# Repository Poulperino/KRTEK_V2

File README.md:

# KRTEK_V2

On essaie on verra bien

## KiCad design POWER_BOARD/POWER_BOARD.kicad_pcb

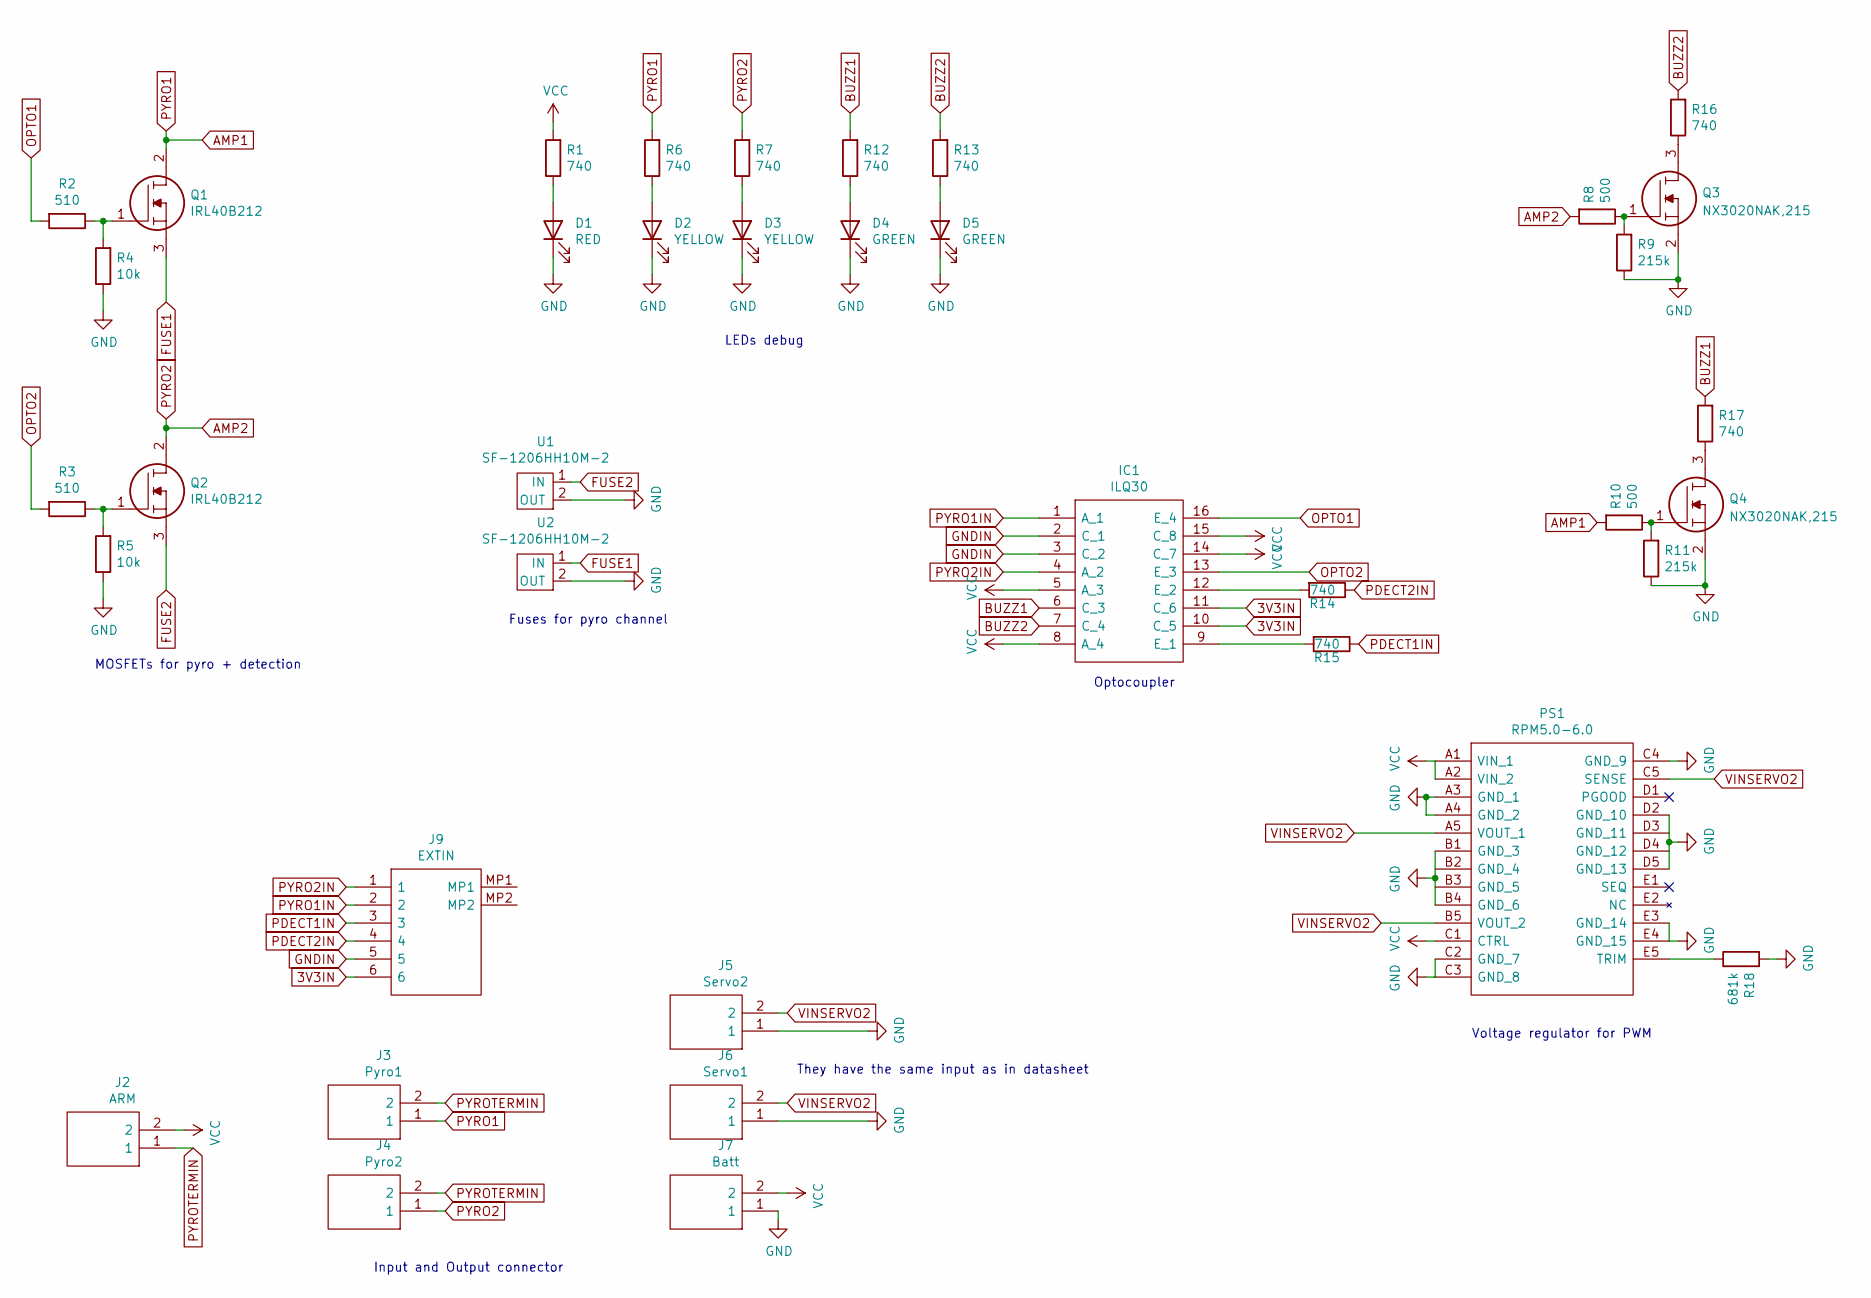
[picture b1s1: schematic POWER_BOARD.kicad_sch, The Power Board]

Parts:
D1: RED; LED_2-SMD_No_Lead_1.7x0.8mm
D2, D3: YELLOW; LED_2-SMD_No_Lead_1.7x0.8mm
D4, D5: GREEN; LED_2-SMD_No_Lead_1.7x0.8mm
IC1: ILQ30; DIP762W60P254L2030H430Q16N; Mouser Part Number 782-ILQ30
J2: ARM; 282834-2_1; Mouser Part Number 571-282834-2
J3: Pyro1; 282834-2_1; Mouser Part Number 571-282834-2
J4: Pyro2; 282834-2_1; Mouser Part Number 571-282834-2
J5: Servo2; 282834-2_1; Mouser Part Number 571-282834-2
J6: Servo1; 282834-2_1; Mouser Part Number 571-282834-2
J7: Batt; 282834-2_1; Mouser Part Number 571-282834-2
J9: EXTIN; 5055670671; Mouser Part Number 538-505567-0671
PS1: RPM5.0-6.0; RPM5060; Mouser Part Number 919-RPM5.0-6.0
Q1, Q2: IRL40B212; TO254P483X1016X1994-3P; Mouser Part Number 942-IRL40B212
Q3, Q4: NX3020NAK,215; SOT-23; Mouser Part Number 942-IRL40B212
R1, R6, R7, R12, R13, R14, R15, R16, R17: 740; R_0603_1608Metric
R2, R3: 510; R_0603_1608Metric
R4, R5: 10k; R_0603_1608Metric
R8, R10: 500; R_0603_1608Metric
R9, R11: 215k; R_0603_1608Metric
R18: 681k; R_0603_1608Metric
U1, U2: SF-1206HH10M-2

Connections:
3V3IN: IC1.10 (C_5), IC1.11 (C_6), J9.6
AMP1: J3.1, Q1.2, R6.2, R10.2
AMP2: J4.1, Q2.2, R7.2, R8.2
BUZZ1: IC1.6 (C_3), R12.2, R17.2
BUZZ2: IC1.7 (C_4), R13.2, R16.2
FUSE1: Q1.3, U2.1 (IN)
FUSE2: Q2.3, U1.1 (IN)
GND: D1.1 (K), D2.1 (K), D3.1 (K), D4.1 (K), D5.1 (K), J5.1, J6.1, J7.1, PS1.A3 (GND_1), PS1.A4 (GND_2), PS1.B1 (GND_3), PS1.B4 (GND_6), PS1.C2 (GND_7), PS1.C3 (GND_8), PS1.C4 (GND_9), PS1.D2 (GND_10), PS1.D5 (GND_13), PS1.E3 (GND_14), PS1.E4 (GND_15), Q3.2, Q4.2, R4.1, R5.1, R9.1, R11.1, R18.2, U1.2 (OUT), U2.2 (OUT)
GNDIN: IC1.2 (C_1), IC1.3 (C_2), J9.5
unnamed: D1.2 (A), R1.1
unnamed: D2.2 (A), R6.1
unnamed: D3.2 (A), R7.1
unnamed: D4.2 (A), R12.1
unnamed: D5.2 (A), R13.1
unnamed: IC1.9 (E_1), R15.2
unnamed: IC1.12 (E_2), R14.2
unnamed: PS1.E5 (TRIM), R18.1
unnamed: Q1.1, R2.1, R4.2
unnamed: Q2.1, R3.1, R5.2
unnamed: Q3.1, R8.1, R9.2
unnamed: Q3.3, R16.1
unnamed: Q4.1, R10.1, R11.2
unnamed: Q4.3, R17.1
OPTO1: IC1.16 (E_4), R2.2
OPTO2: IC1.13 (E_3), R3.2
PDECT1IN: J9.3, R15.1
PDECT2IN: J9.4, R14.1
PYRO1IN: IC1.1 (A_1), J9.2
PYRO2IN: IC1.4 (A_2), J9.1
PYROTERMIN: J2.1, J3.2, J4.2
VCC: IC1.5 (A_3), IC1.8 (A_4), IC1.14 (C_7), IC1.15 (C_8), J2.2, J7.2, PS1.A1 (VIN_1), PS1.A2 (VIN_2), PS1.C1 (CTRL), R1.2
VINSERVO2: J5.2, J6.2, PS1.A5 (VOUT_1), PS1.B5 (VOUT_2), PS1.C5 (SENSE)

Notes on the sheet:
MOSFETs for pyro + detection
Input and Output connector
LEDs debug
Fuses for pyro channel
Optocoupler
Voltage regulator for PWM
They have the same input as in datasheet

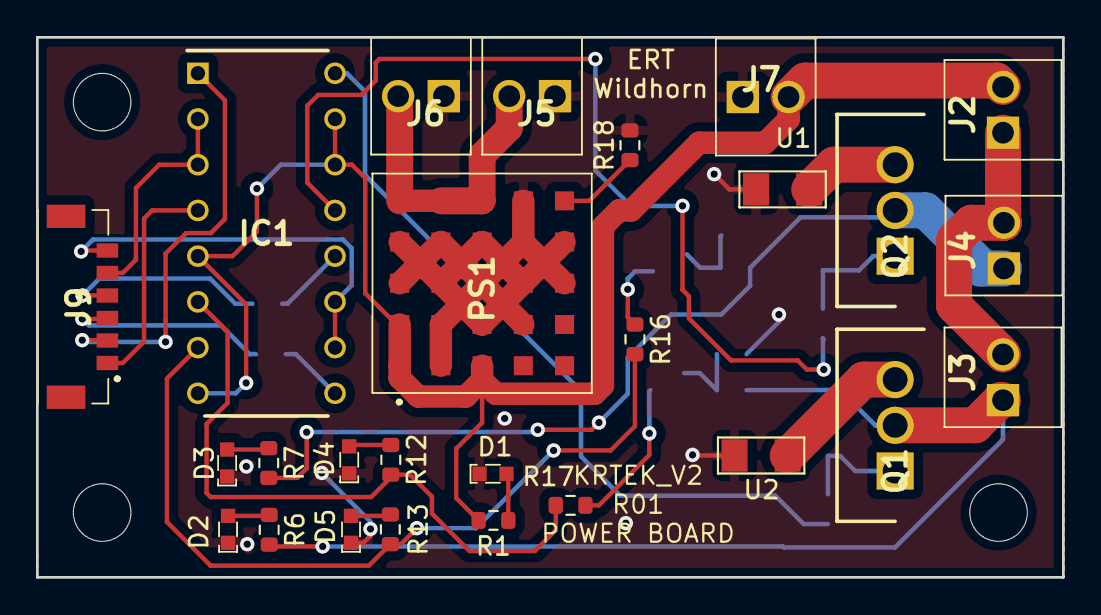
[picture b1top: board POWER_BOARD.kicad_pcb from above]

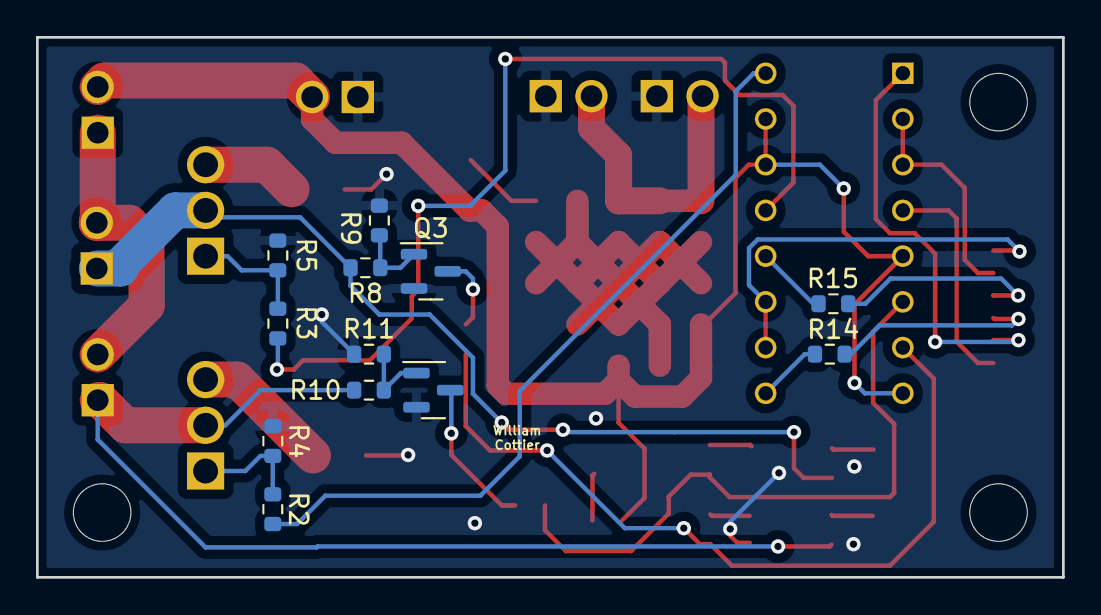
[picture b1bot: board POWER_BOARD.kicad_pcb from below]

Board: 2 copper layers, 57.0 x 30.0 mm, 38 parts (12 on the bottom side), 32 nets.

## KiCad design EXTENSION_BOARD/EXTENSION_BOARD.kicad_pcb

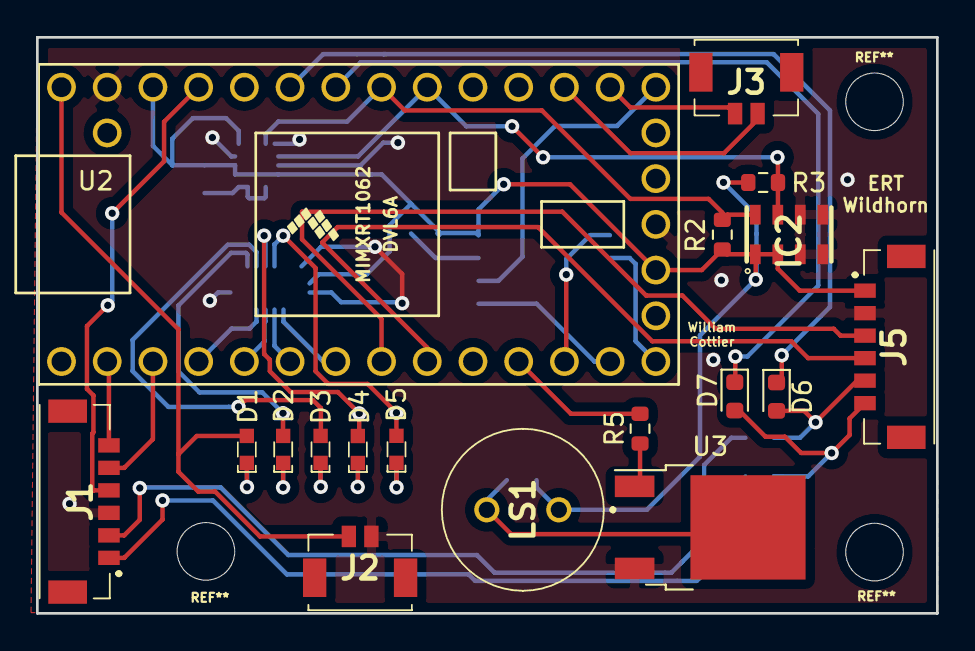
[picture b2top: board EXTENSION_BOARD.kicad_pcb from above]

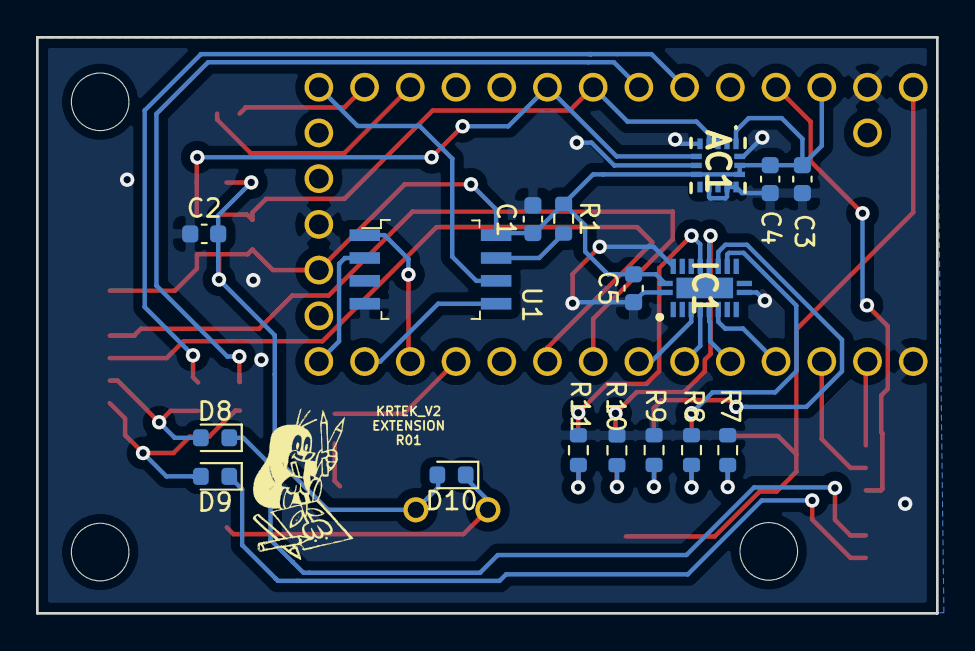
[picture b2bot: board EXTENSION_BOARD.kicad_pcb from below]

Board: 2 copper layers, 50.0 x 32.0 mm, 35 parts (17 on the bottom side), 39 nets.

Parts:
AC1: Accel - H3LIS331DLTR; LIS3DHTR
C1: 100nF; C_0603_1608Metric
C2, C3, C5: 0.1uF; C_0603_1608Metric
C4: 10uF; C_0603_1608Metric
D1: RED; LED_2-SMD_No_Lead_1.7x0.8mm
D2, D3: YELLOW; LED_2-SMD_No_Lead_1.7x0.8mm
D4, D5: GREEN; LED_2-SMD_No_Lead_1.7x0.8mm
D6, D7, D8, D9, D10: DIODE; D_0603_1608Metric
IC1: TeensyBuffer - 74AHCV541ABQX; QFN50P250X450X100-21N-D
IC2: Baro - MS561101BA03-50; MS561101BA03-50
J1: EXTIN; 5055670671
J2: BATT; 5055670281
J3: PWM; 5055670281
J5: EXTOUT; 5055670671
LS1: Buzzer - CST-931AP; CST931AP
R1: 10M; R_0603_1608Metric
R2, R3: 3.3K; R_0603_1608Metric
R5: 10k; R_0603_1608Metric
R7: 500; R_0603_1608Metric
R8, R9, R10, R11: 330; R_0603_1608Metric
U1: Flash - COM-15809; SOIC-8_W5.6mm
U2: Teensy4.0; Teensy40_EXT
U3: MJD148J; TO-252-2

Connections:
+3V3: AC1.1, AC1.8, AC1.14, AC1.15, C1.1, C2.2, C3.1, C4.1, C5.2, D10.2, IC1.20, IC2.1, IC2.2, J5.1, LS1.1, R1.1, R2.2, R3.2, U1.8, U2.16, U2.31
Accel_SCL: AC1.4, IC2.8, R2.1, U2.26
Accel_SDA: AC1.6, IC2.7, R3.1, U2.25
Buzzer: D10.1, LS1.2, U3.2
CS_FLASH: U1.1, U2.12
GLED1: D4.2, IC1.15
GLED2: D5.2, IC1.16
GND: AC1.5, AC1.7, AC1.10, AC1.12, AC1.13, AC1.16, C1.2, C2.1, C3.2, C4.2, C5.1, IC1.1, IC1.10, IC1.19, IC2.3, IC2.4, IC2.5, IC2.6, J1.3, J2.2, J5.2, R7.1, R8.1, R9.1, R10.1, R11.1, U1.4, U2.1, U2.17, U2.32, U3.3
HFREE: J1.4, U2.30
HRX: J1.6, U2.2
HTX: J1.5, U2.3
MISO: U1.2, U2.14
MOSI: U1.5, U2.13
unnamed: D1.1, R7.2
unnamed: D2.1, R8.2
unnamed: D3.1, R9.2
unnamed: D4.1, R10.2
unnamed: D5.1, R11.2
unnamed: R1.2, U1.7
unnamed: R5.1, U3.1
OPYRO1: D6.2, D8.2, J5.5
OPYRO2: D7.2, D9.2, J5.6
PDECT1: J5.3, U2.8
PDECT2: J5.4, U2.9
PWM1: J3.2, U2.21
PWM2: J3.1, U2.22
PYRO1: D8.1, J1.2
PYRO2: D9.1, J1.1
SCLK: U1.6, U2.20
TBuzzer: R5.2, U2.11
TGLED1: IC1.5, U2.6
TGLED2: IC1.4, U2.7
TPyro1OUT: D6.1, U2.28
TPyro2OUT: D7.1, U2.27
TYLED1: IC1.7, U2.4
TYLED2: IC1.6, U2.5
VIN: D1.2, J2.1, U2.33
YLED1: D2.2, IC1.13
YLED2: D3.2, IC1.14

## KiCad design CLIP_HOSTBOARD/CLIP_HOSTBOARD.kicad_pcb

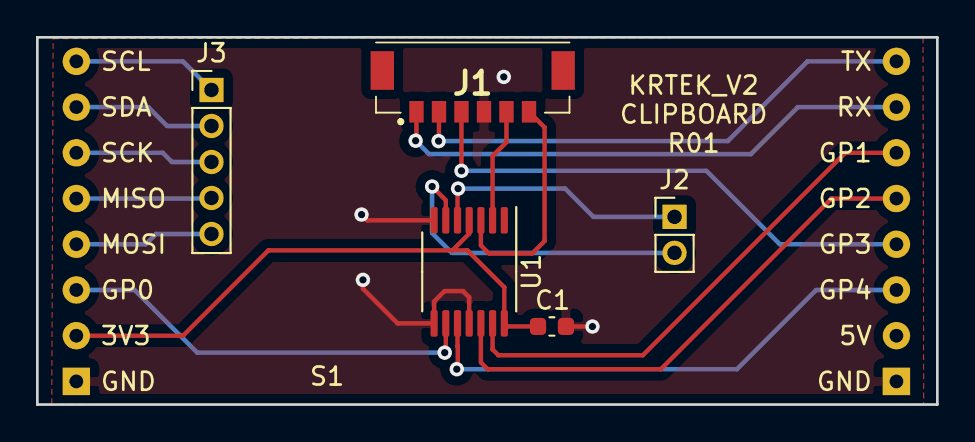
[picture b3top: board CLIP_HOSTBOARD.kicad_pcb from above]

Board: 2 copper layers, 50.0 x 20.4 mm, 6 parts (0 on the bottom side), 18 nets.

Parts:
C1: 0.1uF; C_0603_1608Metric
J1: 505567-0671; 5055670671
J2: 1x2_header; PinHeader_1x02_P2.00mm_Vertical
J3: 1x5_header; PinHeader_1x05_P2.00mm_Vertical
S1: Socket; SOCKET
U1: Buffer; TSSOP-14_4.4x5mm_P0.65mm

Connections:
3V3: C1.2, S1.7, U1.4, U1.14
BFREEIN1: S1.11, U1.10
BFREEIN2: S1.6, U1.9
BFREEOUT1: J2.1, U1.5
BFREEOUT2: J2.2, U1.6
GND: C1.1, J1.4, S1.8, S1.9, U1.7, U1.8, U1.11
HFREE: J1.3, S1.12
HPYRO1: S1.14, U1.13
HPYRO2: S1.13, U1.12
HRX: J1.1, S1.15
HTX: J1.2, S1.16
MISOFREE: J3.4, S1.4
MOSIFREE: J3.5, S1.5
PYRO1: J1.5, U1.2
PYRO2: J1.6, U1.3
SCKFREE: J3.3, S1.3
SCLFREE: J3.1, S1.1
SDAFREE: J3.2, S1.2

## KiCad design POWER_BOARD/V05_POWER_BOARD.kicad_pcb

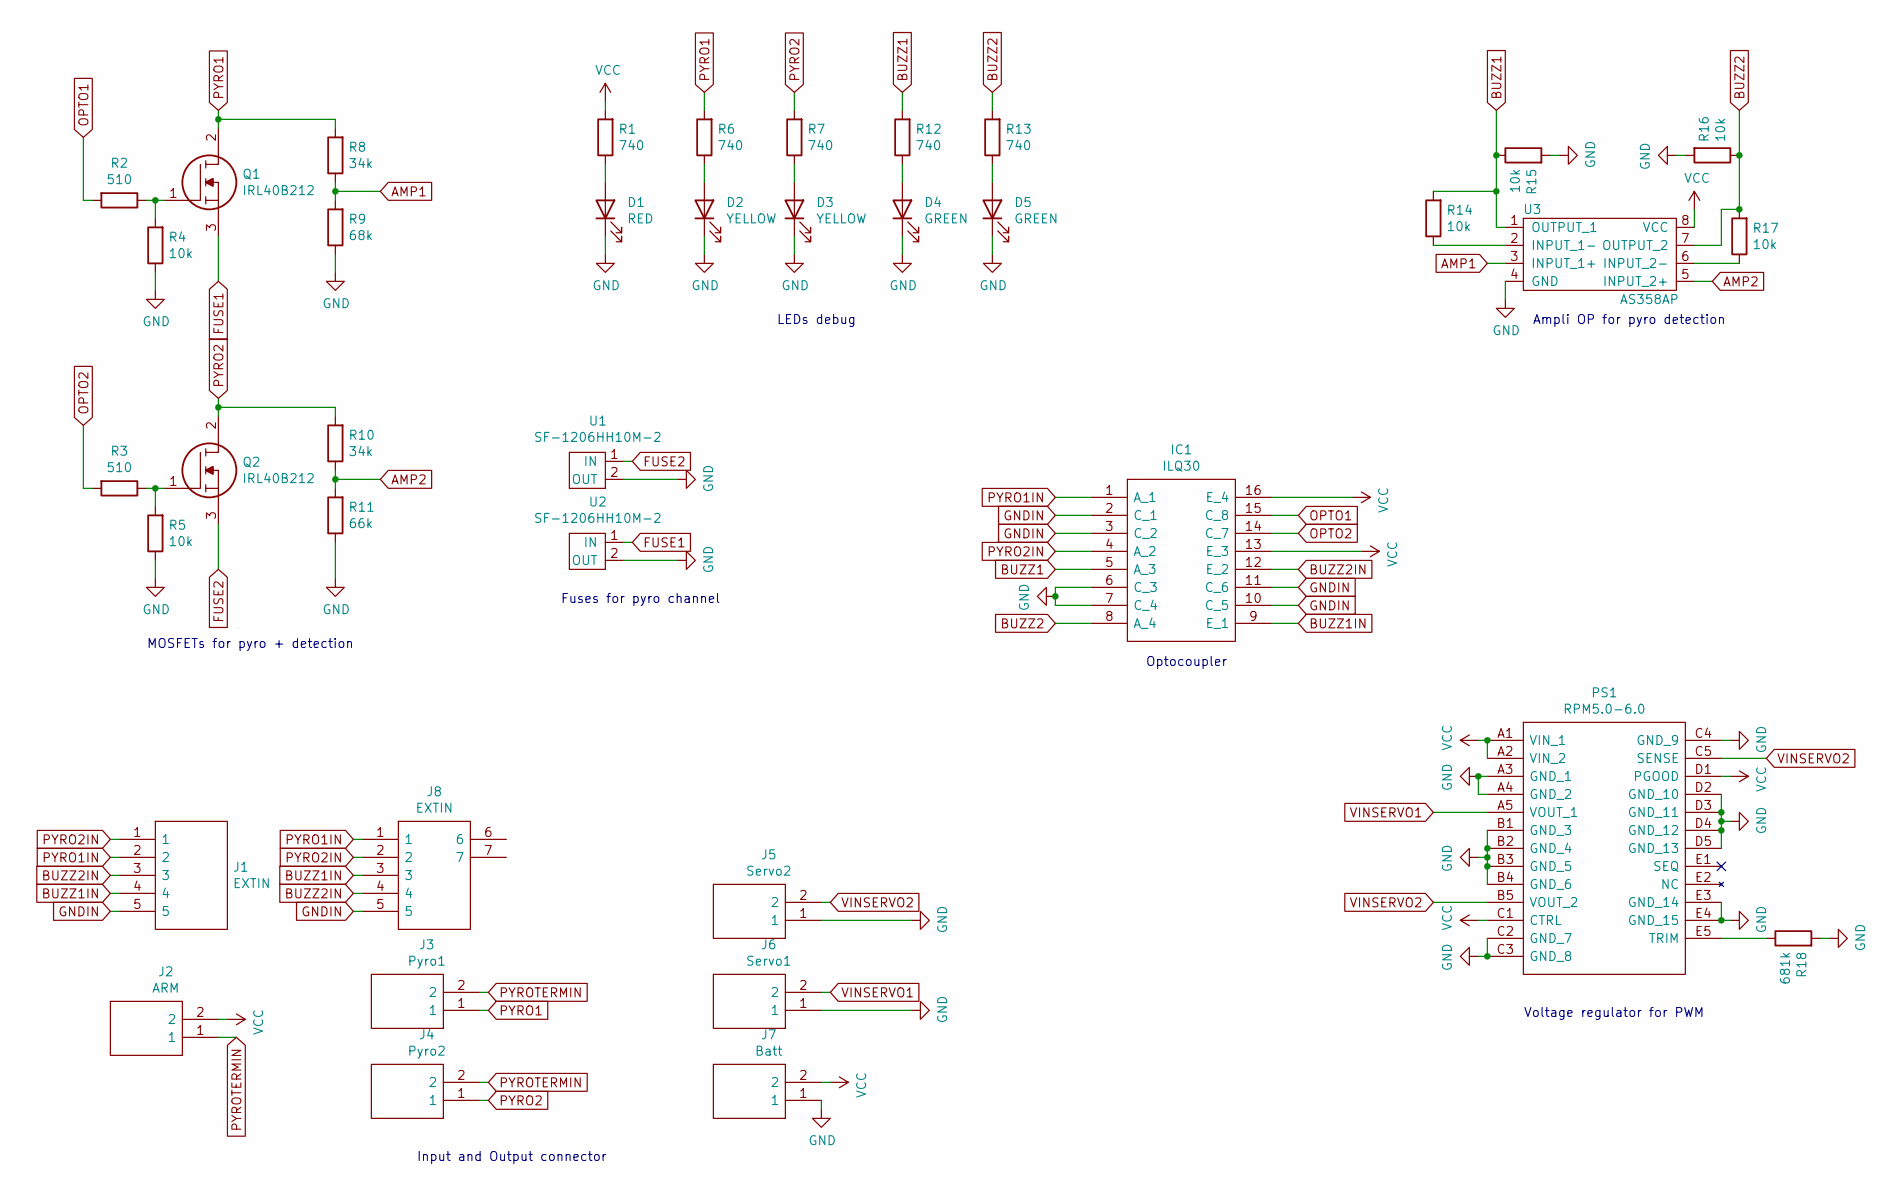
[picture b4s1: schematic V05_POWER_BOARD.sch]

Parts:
D1: RED; LED_2-SMD_No_Lead_1.7x0.8mm
D2, D3: YELLOW; LED_2-SMD_No_Lead_1.7x0.8mm
D4, D5: GREEN; LED_2-SMD_No_Lead_1.7x0.8mm
IC1: ILQ30; DIP762W60P254L2030H430Q16N; Mouser Part Number 782-ILQ30
J1: EXTIN; 2828345; Mouser Part Number 571-282834-5
J2: ARM; 282834-2_1; Mouser Part Number 571-282834-2
J3: Pyro1; 282834-2_1; Mouser Part Number 571-282834-2
J4: Pyro2; 282834-2_1; Mouser Part Number 571-282834-2
J5: Servo2; 282834-2_1; Mouser Part Number 571-282834-2
J6: Servo1; 282834-2_1; Mouser Part Number 571-282834-2
J7: Batt; 282834-2_1; Mouser Part Number 571-282834-2
J8: EXTIN; 5055670571; Mouser Part Number 538-505567-0571
PS1: RPM5.0-6.0; RPM5060; Mouser Part Number 919-RPM5.0-6.0
Q1, Q2: IRL40B212; TO254P483X1016X1994-3P; Mouser Part Number 942-IRL40B212
R1, R6, R7, R12, R13: 740; R_0603_1608Metric
R2, R3: 510; R_0603_1608Metric
R4, R5, R14, R15, R16, R17: 10k; R_0603_1608Metric
R8, R10: 34k; R_0603_1608Metric
R9: 68k; R_0603_1608Metric
R11: 66k; R_0603_1608Metric
R18: 681k; R_0603_1608Metric
U1, U2: SF-1206HH10M-2
U3: AS358AP; AS358AP-PDIP-8

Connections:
AMP1: R8.1, R9.2, U3.3 (INPUT_1+)
AMP2: R10.1, R11.2, U3.5 (INPUT_2+)
BUZZ1: IC1.5 (A_3), R12.2, R14.2, R15.1, U3.1 (OUTPUT_1)
BUZZ1IN: IC1.9 (E_1), J1.4, J8.3
BUZZ2: IC1.8 (A_4), R13.2, R16.1, R17.2, U3.7 (OUTPUT_2)
BUZZ2IN: IC1.12 (E_2), J1.3, J8.4
FUSE1: Q1.3, U2.1 (IN)
FUSE2: Q2.3, U1.1 (IN)
GND: D1.1 (K), D2.1 (K), D3.1 (K), D4.1 (K), D5.1 (K), IC1.6 (C_3), IC1.7 (C_4), J5.1, J6.1, J7.1, PS1.A3 (GND_1), PS1.A4 (GND_2), PS1.B1 (GND_3), PS1.B2 (GND_4), PS1.B3 (GND_5), PS1.B4 (GND_6), PS1.C2 (GND_7), PS1.C3 (GND_8), PS1.C4 (GND_9), PS1.D2 (GND_10), PS1.D3 (GND_11), PS1.D4 (GND_12), PS1.D5 (GND_13), PS1.E3 (GND_14), PS1.E4 (GND_15), R4.1, R5.1, R9.1, R11.1, R15.2, R16.2, R18.2, U1.2 (OUT), U2.2 (OUT), U3.4 (GND)
GNDIN: IC1.2 (C_1), IC1.3 (C_2), IC1.10 (C_5), IC1.11 (C_6), J1.5, J8.5
unnamed: D1.2 (A), R1.1
unnamed: D2.2 (A), R6.1
unnamed: D3.2 (A), R7.1
unnamed: D4.2 (A), R12.1
unnamed: D5.2 (A), R13.1
unnamed: PS1.E5 (TRIM), R18.1
unnamed: Q1.1, R2.1, R4.2
unnamed: Q2.1, R3.1, R5.2
unnamed: R14.1, U3.2 (INPUT_1-)
unnamed: R17.1, U3.6 (INPUT_2-)
OPTO1: IC1.15 (C_8), R2.2
OPTO2: IC1.14 (C_7), R3.2
PYRO1: J3.1, Q1.2, R6.2, R8.2
PYRO1IN: IC1.1 (A_1), J1.2, J8.1
PYRO2: J4.1, Q2.2, R7.2, R10.2
PYRO2IN: IC1.4 (A_2), J1.1, J8.2
PYROTERMIN: J2.1, J3.2, J4.2
VCC: IC1.13 (E_3), IC1.16 (E_4), J2.2, J7.2, PS1.A1 (VIN_1), PS1.A2 (VIN_2), PS1.C1 (CTRL), PS1.D1 (PGOOD), R1.2, U3.8 (VCC)
VINSERVO1: J6.2, PS1.A5 (VOUT_1)
VINSERVO2: J5.2, PS1.B5 (VOUT_2), PS1.C5 (SENSE)

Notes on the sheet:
LEDs debug
MOSFETs for pyro + detection
Fuses for pyro channel
Input and Output connector
Voltage regulator for PWM
Optocoupler
Ampli OP for pyro detection

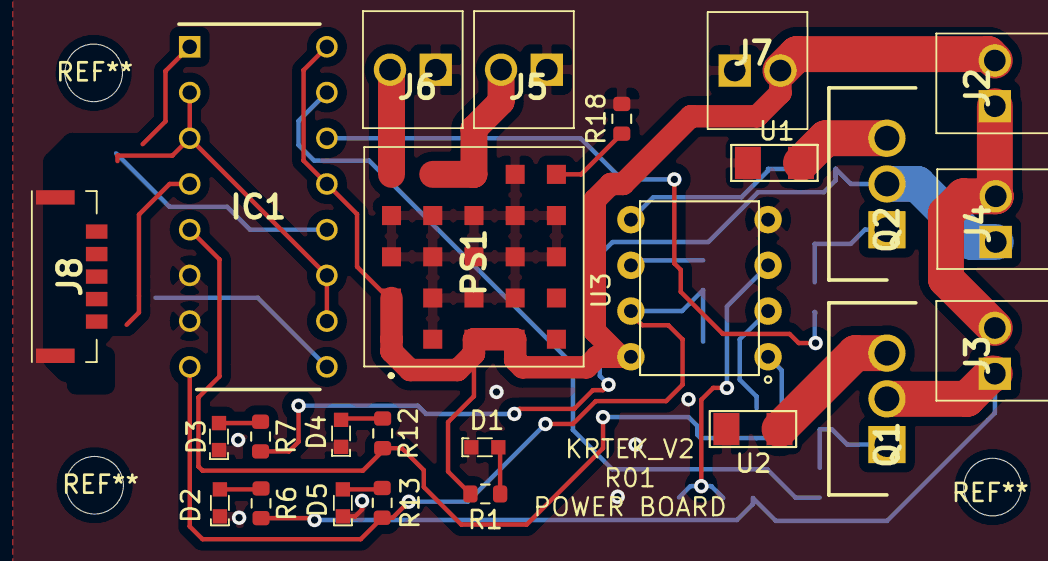
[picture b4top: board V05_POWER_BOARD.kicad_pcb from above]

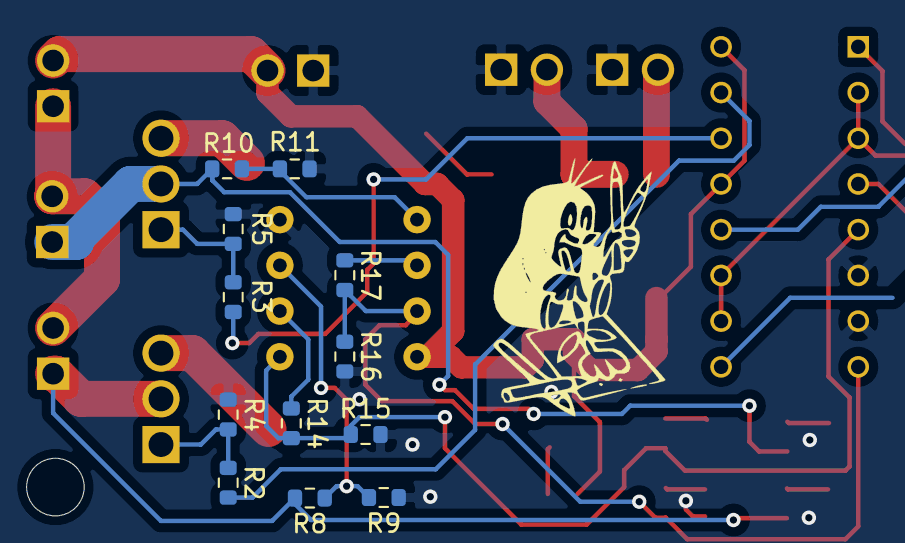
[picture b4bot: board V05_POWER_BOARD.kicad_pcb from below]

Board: 2 copper layers, 37 parts (12 on the bottom side), 30 nets.

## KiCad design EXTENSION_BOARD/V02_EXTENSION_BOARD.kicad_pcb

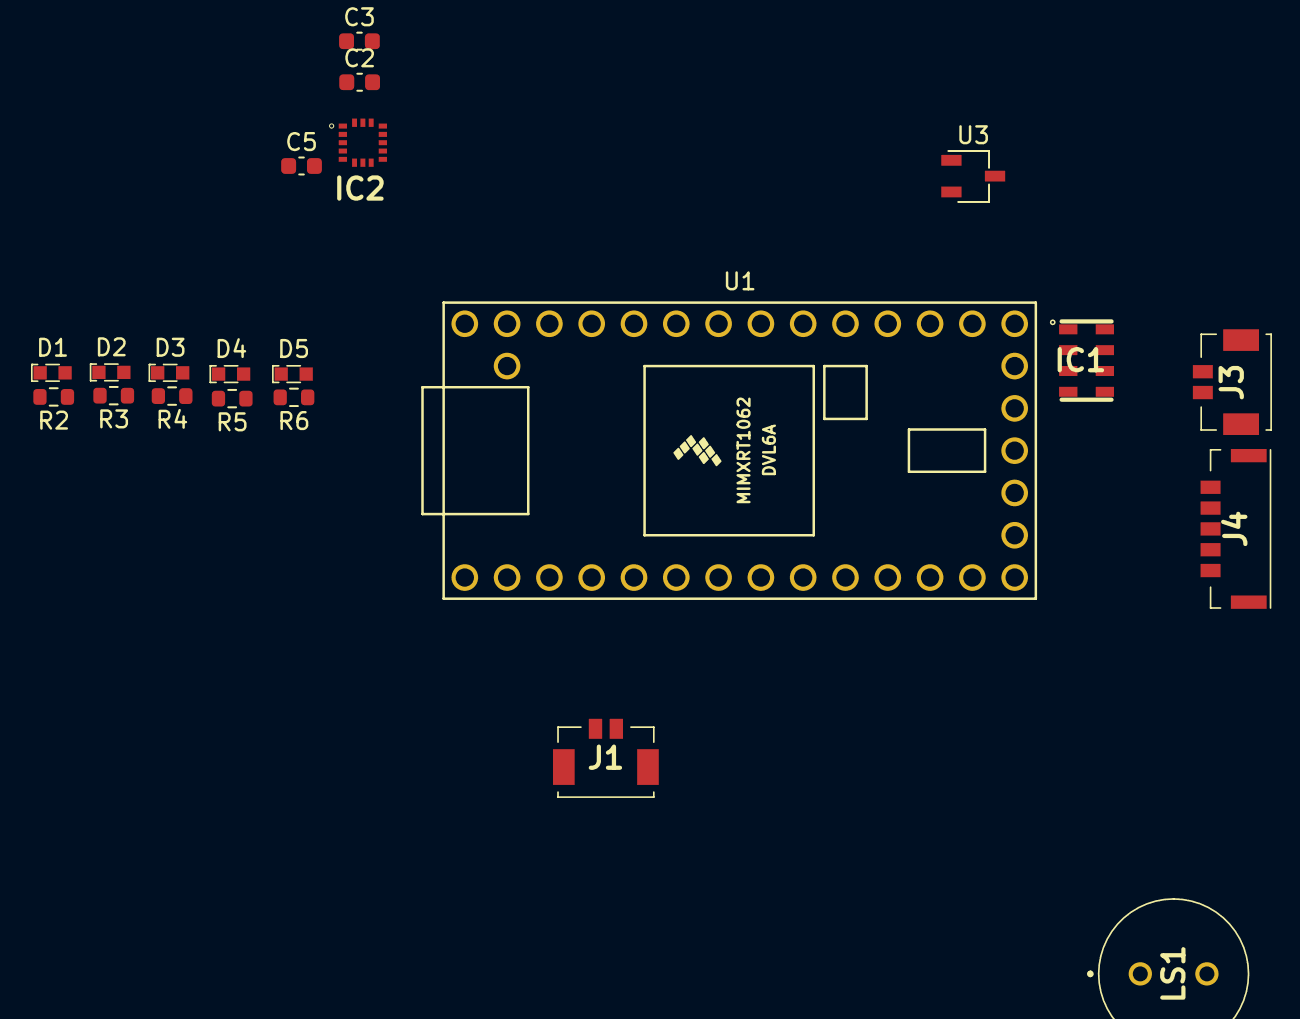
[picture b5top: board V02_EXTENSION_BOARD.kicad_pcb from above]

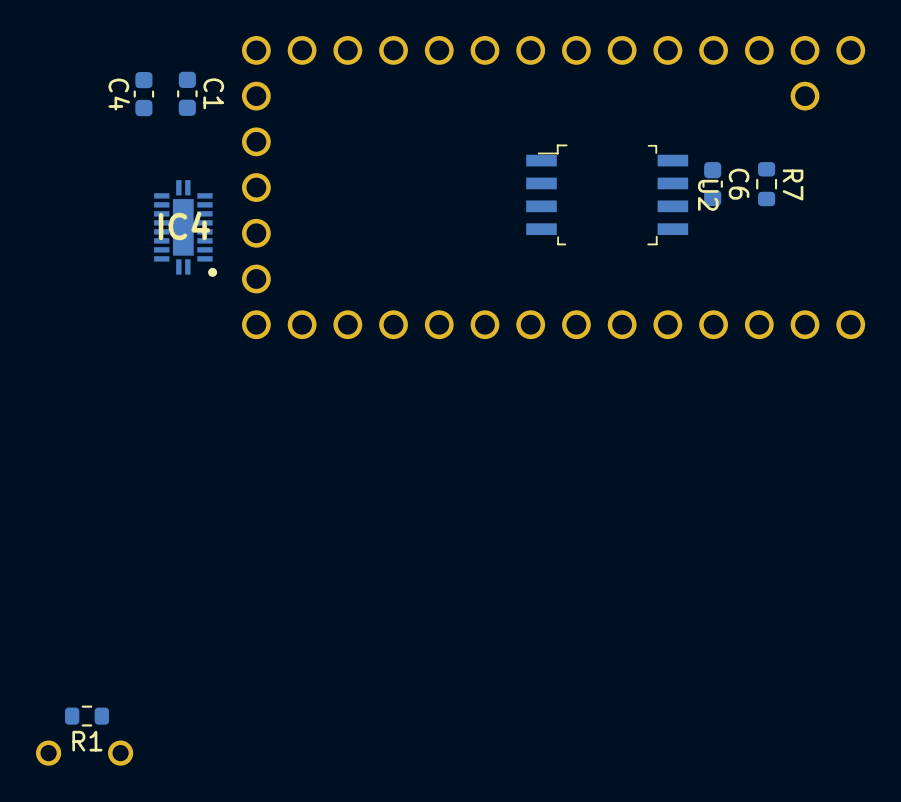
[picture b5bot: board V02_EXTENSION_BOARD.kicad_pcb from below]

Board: 2 copper layers, 28 parts (7 on the bottom side), 25 nets, no tracks yet.

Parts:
C1: 100nF; C_0603_1608Metric
C2: 0.1uF; C_0603_1608Metric
C3: 10nF; C_0603_1608Metric
C4: 2.2uF; C_0603_1608Metric
C5: 0.47uF; C_0603_1608Metric
C6: 22pF; C_0603_1608Metric
D1: RED; LED_2-SMD_No_Lead_1.7x0.8mm
D2, D3: YELLOW; LED_2-SMD_No_Lead_1.7x0.8mm
D4, D5: GREEN; LED_2-SMD_No_Lead_1.7x0.8mm
IC1: Baro; MS561101BA03-50
IC2: ICM-20608-G; PULL-BACK-QFN-16
IC4: TeensyBuffer; QFN50P250X450X100-21N-D
J1: BATT; 5055670281
J3: PWM; 5055670281
J4: EXTOUT; 5055670571
LS1: Buzzer; CST931AP
R1: 1k; R_0603_1608Metric
R2: 740; R_0603_1608Metric
R3, R4, R5, R6: 330; R_0603_1608Metric
R7: 10M; R_0603_1608Metric
U1: Teensy4.0; Teensy40_EXT
U2: COM-15809; SOIC-8_W5.6mm
U3: MOSBuzzer; TSOT-23

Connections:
3V3: C1.2, C2.1, C3.1, C4.1, C6.1, IC1.1, IC2.1, IC2.16, R7.1, U1.16, U1.31, U2.8, U3.3
BUZZ1: IC4.14, J4.3
BUZZ2: IC4.13, J4.4
Buzzer: LS1.1, R1.1, U3.2
GLED1: D4.2, IC4.16
GLED2: D5.2, IC4.15
GND: C1.1, C2.2, C3.2, C4.2, C5.1, C6.2, IC1.2, IC1.3, IC2.9, IC2.10, IC2.11, IC2.12, IC2.13, IC2.15, IC4.1, IC4.10, IC4.19, J1.1, J4.5, LS1.2, R1.2, R2.1, R3.1, R4.1, R5.1, R6.1, U1.1, U1.17, U1.32, U2.4
MISO: IC1.6, U2.2
MOSI: IC1.7, U2.5
unnamed: C5.2, IC2.14
unnamed: D1.1, R2.2
unnamed: D2.1, R3.2
unnamed: D3.1, R4.2
unnamed: D4.1, R5.2
unnamed: D5.1, R6.2
unnamed: R7.2, U2.7
SCLK: IC1.8, IC2.2, U2.6
TBuzzer: U1.8, U3.1
TGLED1: IC4.4, U1.6
TGLED2: IC4.5, U1.7
TYLED1: IC4.2, U1.4
TYLED2: IC4.3, U1.5
VIN: IC4.20, J1.2, U1.33
YLED1: D2.2, IC4.18
YLED2: D3.2, IC4.17

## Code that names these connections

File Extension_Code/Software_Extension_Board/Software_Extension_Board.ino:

/********************************************************************************/
/*              
 *              This is a program for the Teensy 4.0 
 *                On the KRTEK_V2 Extension Board
 *               
 *               
 *               First sketch
 *               
 *               William Cottier, 19.11.2021
 *               
 *               
 */
/********************************************************************************/

/********************************************************************************/ 
//LIBRARIES INCLUDES
/********************************************************************************/ 
#include <Wire.h>
#include <baro_MS5611.h>
#include <accel_H3LIS331DL.h>
#include "UART_Protocol.h"
#include "Serial_Comm.h"
#include "UART_Protocol_Master.h"
#include "UART_Protocol_Slave.h"
/********************************************************************************/ 
//VARIABLE DECLARATION
/********************************************************************************/ 
//Pyro pins
const int TPyro2OUT = 20;
const int TPyro1OUT = 21;

//LEDs pins
const int TYLED1 = 2;
const int TYLED2 = 3;
const int TGLED1 = 4;
const int TGLED2 = 5;

//From power board Pyro Detection pins (For buzzer)
const int PDECT1 = 6;
const int PDECT2 = 7;

//Extension buzzer pin
const int TBuzzer = 9;

//PWM pins
const int PWM1 = 14;
const int PWM2 = 15;

//Baro I2C pins
const int Baro_SCL = 16;
const int Baro_SDA = 17;

//Accel I2C pins
const int Accel_SDA = 18;
const int Accel_SCL = 19;

//Flash SPI pins
const int CS_FLASH = 10;
const int FLASH_MOSI = 11;
const int FLASH_MISO = 12;
const int FLASH_SCLK = 13;

// RX TX
const int HRX = 0;
const int HTX = 1;

//HFree pin
const int HFREE = 30;

//Acceleration variables
int xAcc = 0;
int yAcc = 0;
int zAcc = 0;

//Baro initialization
Baro Baro;

//Accel initialization
Accel Accel;


/********************************************************************************/ 
//SETUP
/********************************************************************************/ 

void setup() {
  
  //Pin definitions
  pinMode(TPyro2OUT, OUTPUT);
  pinMode(TPyro1OUT, OUTPUT);
  pinMode(TYLED1, OUTPUT);
  pinMode(TYLED2, OUTPUT);
  pinMode(TGLED1, OUTPUT);
  pinMode(TGLED2, OUTPUT);
  pinMode(TBuzzer, OUTPUT);
  pinMode(PWM1, OUTPUT);
  pinMode(PWM2, OUTPUT);
  
  pinMode(PDECT1, INPUT);
  pinMode(PDECT2, INPUT);
  pinMode(HFREE, INPUT);

  //Initialize I2C communication as MASTER
  Wire.begin();

  //Initialize Serial communication (for computer)
  Serial.begin(9600);
  //Initialize Serial communication (for Iacoboard)
  HWSERIAL.begin(9600);

  //Baro setup
  Baro.Setup();
  //Accelerometer setup
  Accel.Setup();

}

void loop() {
  /*
  //just a buzzer test
  BuzzBIP(); //beeps 100ms every sec

  //Get accelerometer's datas
  xAcc = Accel.getAccData(0); //0 for the x acceleration
  yAcc = Accel.getAccData(2); //2 for the y acceleration
  zAcc = Accel.getAccData(4); //4 for the z acceleration
  delay(100);
  */

  Serial.println("This is written in the terminal");

}

/********************************************************************************/
//  The buzzer and the LEDs
/********************************************************************************/
void BuzzBIP(){
  int buzzerPitch = 400; //The sound it makes
  int bipTime = 100; //Time in ms it bips
  //PWM should work through a BJT
  tone(TBuzzer,buzzerPitch,bipTime);
  delay(1000);
  return;
}

void LEDOn(int LEDpin){
  //Just because I find it clearer than
  //digitalWrite everywhere
  digitalWrite(LEDOn,HIGH);
  return;
}

void LEDOff(int LEDpin){
  //Just because I find it clearer than
  //digitalWrite everywhere
  digitalWrite(LEDOn,LOW);
  return;
}

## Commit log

2021-11-09 Update fp-info-cache
2021-11-09 Update fp-lib-table
2021-11-09 Update POWER_BOARD.sch-bak
2021-11-09 Update sym-lib-table
2021-11-09 Update EXTENSION_BOARD.kicad_pcb-bak
2021-11-09 Update EXTENSION_BOARD.sch-bak
2021-11-12 Create CLIP_HOSTBOARD.sch-bak
2021-11-12 Create sym-lib-table
2021-11-12 worked
2021-11-12 Revert "Create CLIP_BOARD.dcm"
    This reverts commit 47ffac65a46468dc5f7665e39c37403d6dcd45ff.
2021-11-12 Revert "Create CLIP_BOARD.lib"
    This reverts commit d691936a8c66bce720e619798eb563f1b5ff8b78.
2021-11-12 Revert "Revert "Create CLIP_BOARD.lib""
    This reverts commit f93a0fd505c0df7b6a57b2c785e60f2b3f4e6847.
2021-11-15 Worked again
2021-11-19 Sent schematics to review
2021-11-25 last changes
2021-11-25 gerbers
2021-12-23 Update soft
2021-12-23 upupdate
2022-11-03 last commit
2022-11-03 real last commit

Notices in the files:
POWER_BOARD/POWER_BOARD.kicad_sch:
EPFL Rocket Team all rights reserved
